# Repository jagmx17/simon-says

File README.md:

# Simon-Says
A simon says game built on a PCB. It uses four keyboard switches and four LEDs to play. This project has helped me begin working on my foundations in PCB design.

## 3D Model

## Schematic

## PCB Design

## Bill of Materials
|Quantity|Item                    |Cost (USD)|Link                                                                                                     |
|--------|------------------------|----------|---------------------------------------------------------------------------------------------------------|
|1       |Seeed Studio XIAO RP2040|$4.88     |https://www.digikey.com/en/products/detail/seeed-technology-co-ltd/102010428/14672129                    |
|1       |XIAO RP2040 Header Pins |$0.25     |https://www.digikey.com/en/products/detail/seeed-technology-co-ltd/102010490/19176770                    |
|4       |Cherry MX Key Switches  |$5.00     |https://www.digikey.com/en/products/detail/cherry-americas-llc/MX1A-C1NW/280855                          |
|4       |120 Ohm Resistors       |$0.35     |https://www.digikey.com/en/products/detail/yageo/CFR-25JB-52-120R/389                                    |
|10      |Green LEDs              |$0.67     |https://www.digikey.com/en/products/detail/american-bright-optoelectronics-corporation/BL-B2141Q/22486916|
|1       |Translucent Keycaps     |$4.95     |https://www.digikey.com/en/products/detail/adafruit-industries-llc/4956/13997776                         |
|1       |PCB                     |$3.12     |                                                                                                         |
|        |Subtotal:               |$19.22    |                                                                                                         |

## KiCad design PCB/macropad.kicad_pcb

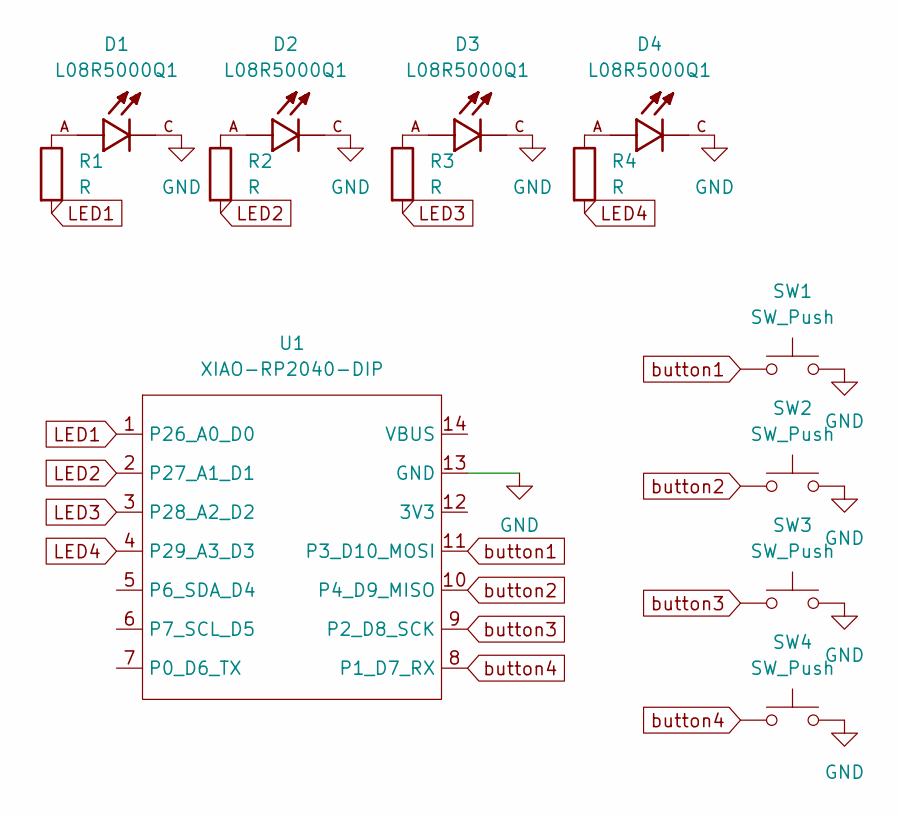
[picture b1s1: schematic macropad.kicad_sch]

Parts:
D1, D2, D3, D4: L08R5000Q1; LEDRD254W57D500H1070; PARTREV NA
R1, R2, R3, R4: R; R_Axial_DIN0204_L3.6mm_D1.6mm_P5.08mm_Vertical
SW1, SW2, SW3, SW4: SW_Push; SW_Cherry_MX_1.00u_PCB
U1: XIAO-RP2040-DIP

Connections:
GND: D1.C, D2.C, D3.C, D4.C, SW1.2, SW2.2, SW3.2, SW4.2, U1.13 (GND)
LED1: R1.2, U1.1 (P26_A0_D0)
LED2: R2.2, U1.2 (P27_A1_D1)
LED3: R3.2, U1.3 (P28_A2_D2)
LED4: R4.2, U1.4 (P29_A3_D3)
unnamed: D1.A, R1.1
unnamed: D2.A, R2.1
unnamed: D3.A, R3.1
unnamed: D4.A, R4.1
button1: SW1.1, U1.11 (P3_D10_MOSI)
button2: SW2.1, U1.10 (P4_D9_MISO)
button3: SW3.1, U1.9 (P2_D8_SCK)
button4: SW4.1, U1.8 (P1_D7_RX)

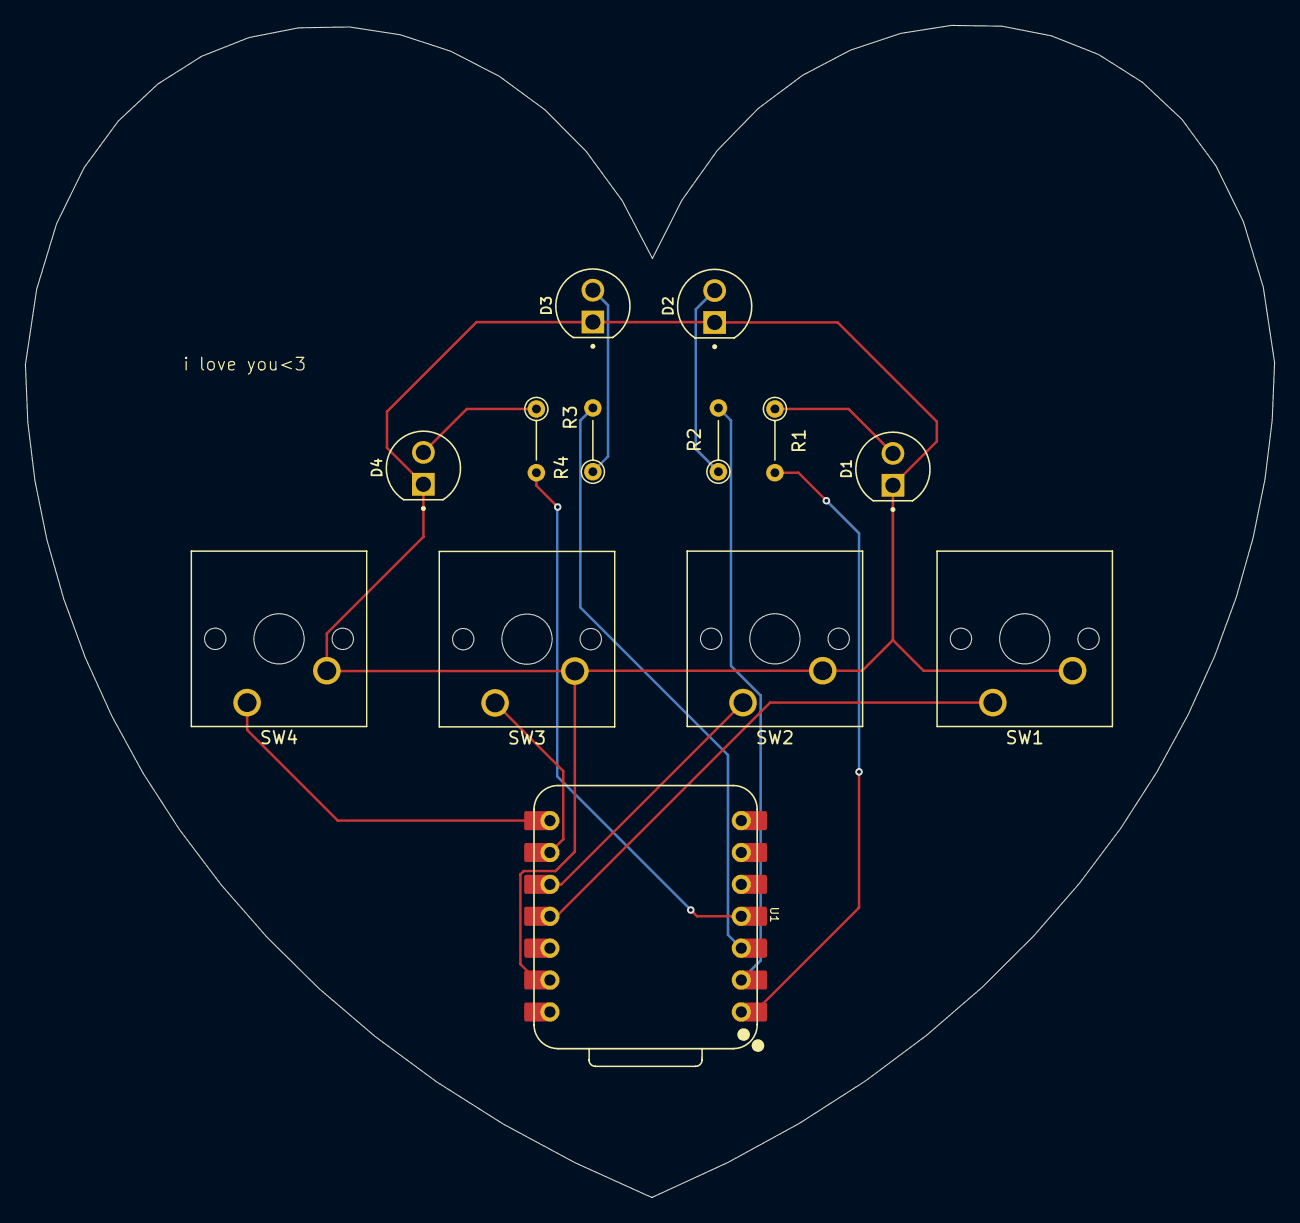
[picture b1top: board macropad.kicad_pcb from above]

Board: 2 copper layers, 99.5 x 93.4 mm, 13 parts (0 on the bottom side), 13 nets.

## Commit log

2026-06-10 Update README with schematic and PCB design
    Added schematic and PCB design images to README.
2026-06-10 Add 3D Model image to README
    Added a section for 3D model with an image.
2026-06-10 Enhance README with project details and images
    Updated project description and added sections for 3D Model, Schematic, and PCB Design.
2026-06-10 Create PCB folder
2026-06-10 Added KiCad files
2026-06-10 Create placeholder
2026-06-10 Moved KiCad files into the PCB folder
2026-06-10 Added Bill of Materials
2026-06-10 Update README to include Bill of Materials
    Added a Bill of Materials section with item details and links.
2026-06-10 Fix project title formatting in README
    Updated project title from 'simon-says' to 'Simon-Says'.
2026-06-10 Added firmware
2026-06-10 Enhance README with details about game components
    Expanded project description to include details about the components used.
2026-06-12 Update README with new images and BOM details
    Added additional images for the 3D model and PCB design sections.
2026-06-12 Update PCB design image in README
    Replaced PCB design image with a new one.
2026-06-12 Added updated KiCad files
